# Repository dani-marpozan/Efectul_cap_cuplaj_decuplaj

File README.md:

# Eefectul capacitatilor de cuplare/decuplare

Model 3D

## Schematic

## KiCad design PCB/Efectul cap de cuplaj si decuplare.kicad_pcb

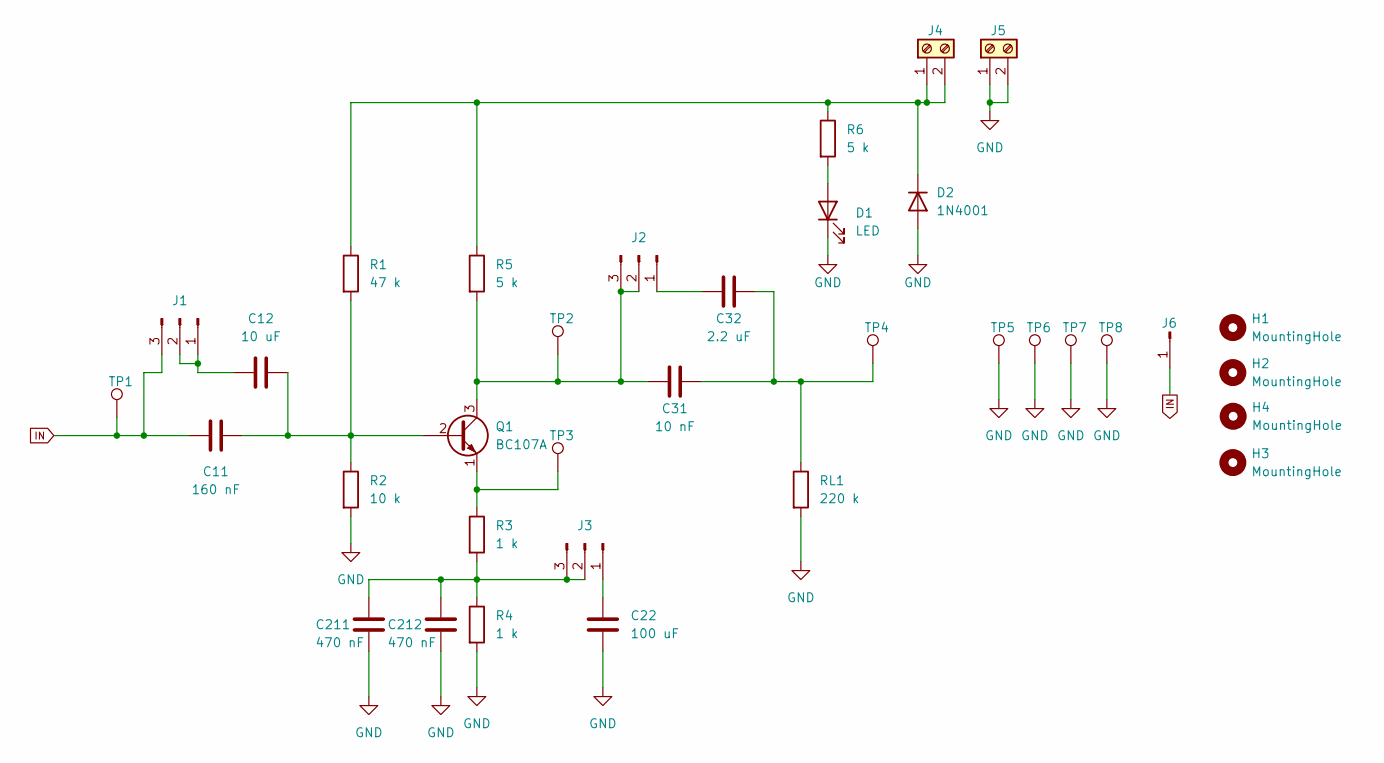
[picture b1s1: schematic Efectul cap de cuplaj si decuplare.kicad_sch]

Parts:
C11: 160 nF; Cap_160 nF
C12: 10 uF; CP_Radial_D6.3mm_P2.50mm
C22: 100 uF; CP_Radial_D8.0mm_P3.50mm
C31: 10 nF; C_Rect_L11.5mm_W9.5mm_P10.00mm_MKT
C32: 2.2 uF; C_Radial_D5.0mm_H11.0mm_P2.00mm
C211, C212: 470 nF; C_Rect_L7.2mm_W5.5mm_P5.00mm_FKS2_FKP2_MKS2_MKP2
D1: LED; LED_D5.0mm
D2: 1N4001; D_DO-41_SOD81_P10.16mm_Horizontal
H1, H2, H3, H4: MountingHole; MountingHole_3.2mm_M3_ISO7380_Pad_TopBottom
J1, J2, J3: Conn_01x03_Male; PinHeader_1x03_P2.54mm_Vertical
J4, J5: Screw_Terminal_01x02; TerminalBlock_Phoenix_MKDS-1,5-2_1x02_P5.00mm_Horizontal
J6: Conn_01x01_Male; TestPoint
Q1: BC107A; TO-18-3
R1: 47 k; R_Axial_DIN0207_L6.3mm_D2.5mm_P10.16mm_Horizontal
R2: 10 k; R_Axial_DIN0207_L6.3mm_D2.5mm_P10.16mm_Horizontal
R3, R4: 1 k; R_Axial_DIN0207_L6.3mm_D2.5mm_P10.16mm_Horizontal
R5, R6: 5 k; R_Axial_DIN0207_L6.3mm_D2.5mm_P10.16mm_Horizontal
RL1: 220 k; R_Axial_DIN0207_L6.3mm_D2.5mm_P10.16mm_Horizontal
TP1, TP2, TP3, TP4: TestPoint; Kesytone TP Multipurpose 5013
TP5, TP6, TP7, TP8: TestPoint

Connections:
GND: C22.2, C211.2, C212.2, D1.1 (K), D2.2 (A), J5.1, J5.2, R2.2, R4.2, RL1.2, TP5.1, TP6.1, TP7.1, TP8.1
IN: C11.2, J1.3, J6.1, TP1.1
unnamed: C31.2, C32.2, RL1.1, TP4.1
unnamed: D1.2 (A), R6.2
unnamed: D2.1 (K), J4.1, J4.2, R1.1, R5.1, R6.1
unnamed: C12.2, J1.1, J1.2
unnamed: C32.1, J2.1
unnamed: C31.1, J2.2, J2.3, Q1.3 (C), R5.2, TP2.1
unnamed: C22.1, J3.1
unnamed: C211.1, C212.1, J3.2, J3.3, R3.2, R4.1
unnamed: C11.1, C12.1, Q1.2 (B), R1.2, R2.1
unnamed: Q1.1 (E), R3.1, TP3.1

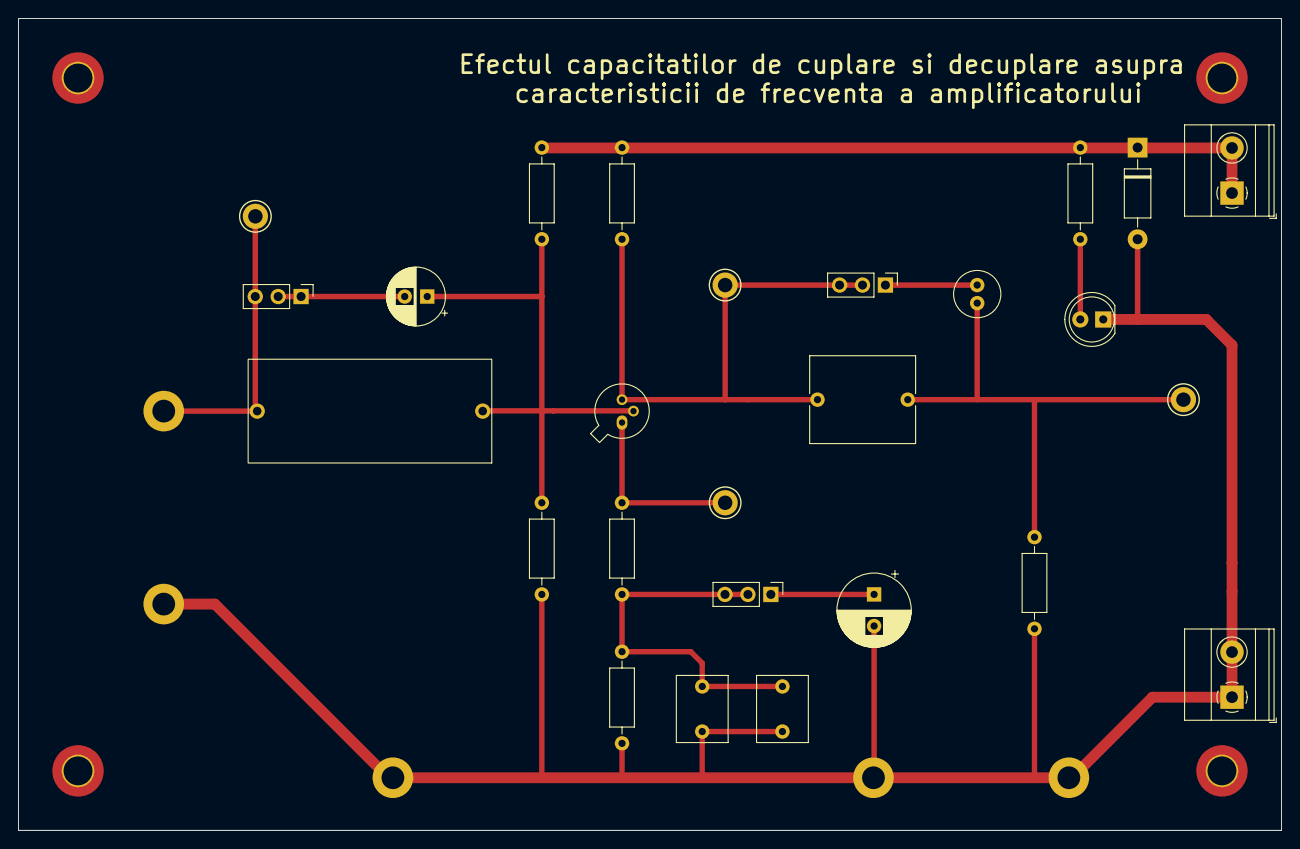
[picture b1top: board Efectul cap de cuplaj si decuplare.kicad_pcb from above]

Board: 2 copper layers, 140.0 x 90.0 mm, 35 parts (0 on the bottom side), 12 nets.

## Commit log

2023-03-21 firs commit
